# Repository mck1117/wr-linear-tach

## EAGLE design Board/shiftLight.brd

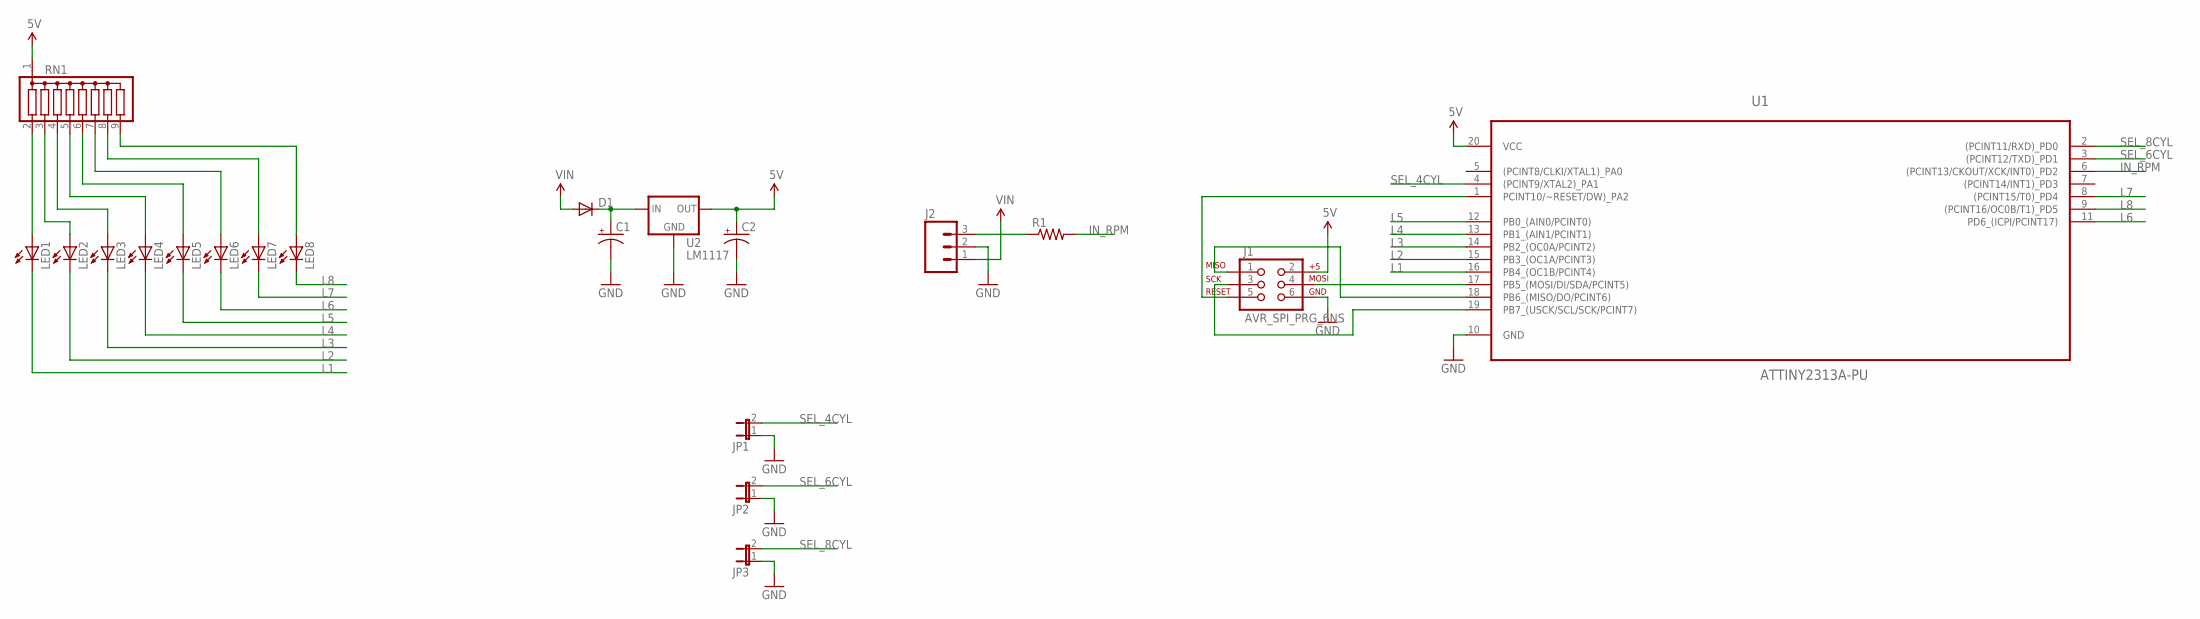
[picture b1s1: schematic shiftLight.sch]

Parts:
C1, C2: CPOL-USE3.5-8; E3,5-8
D1: DIODEPTH; DIODE-1N4001
J1: AVR_SPI_PRG_6NS; 2X3-NS
J2: M03SCREW; SCREWTERMINAL-3.5MM-3
JP1, JP2, JP3: JUMPER-2SMD-NO; SJ_2S-NO
LED1, LED2, LED3, LED4, LED5, LED6, LED7, LED8: LED5MM
R1: RESISTORPTH-1/4W; AXIAL-0.4
RN1: G08R; SIL9
U1: ATTINY2313A-PU; DIP254P762X533-20
U2: LM1117; TO-220-ALT

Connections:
5V: C2.+, J1.2, RN1.1, U1.20 (VCC), U2.OUT
GND: C1.-, C2.-, J1.6, J2.2, JP1.1, JP2.1, JP3.1, U1.10 (GND), U2.GND
IN_RPM: R1.P$2 (2), U1.6 ((PCINT13/CKOUT/XCK/INT0)_PD2)
L1: LED1.K (C), U1.16 (PB4_(OC1B/PCINT4))
L2: LED2.K (C), U1.15 (PB3_(OC1A/PCINT3))
L3: LED3.K (C), U1.14 (PB2_(OC0A/PCINT2))
L4: LED4.K (C), U1.13 (PB1_(AIN1/PCINT1))
L5: LED5.K (C), U1.12 (PB0_(AIN0/PCINT0))
L6: LED6.K (C), U1.11 (PD6_(ICPI/PCINT17))
L7: LED7.K (C), U1.8 ((PCINT15/T0)_PD4)
L8: LED8.K (C), U1.9 ((PCINT16/OC0B/T1)_PD5)
unnamed: LED1.A, RN1.2
unnamed: LED2.A, RN1.3
unnamed: LED3.A, RN1.4
unnamed: LED4.A, RN1.5
unnamed: LED5.A, RN1.6
unnamed: LED6.A, RN1.7
unnamed: LED7.A, RN1.8
unnamed: J2.3, R1.P$1 (1)
unnamed: C1.+, D1.C, U2.IN
unnamed: J1.4, U1.17 (PB5_(MOSI/DI/SDA/PCINT5))
unnamed: J1.3, U1.19 (PB7_(USCK/SCL/SCK/PCINT7))
unnamed: J1.1, U1.18 (PB6_(MISO/DO/PCINT6))
unnamed: J1.5, U1.1 (PCINT10/~RESET/DW)_PA2)
unnamed: LED8.A, RN1.9
SEL_4CYL: JP1.2, U1.4 ((PCINT9/XTAL2)_PA1)
SEL_6CYL: JP2.2, U1.3 ((PCINT12/TXD)_PD1)
SEL_8CYL: JP3.2, U1.2 ((PCINT11/RXD)_PD0)
VIN: D1.A, J2.1

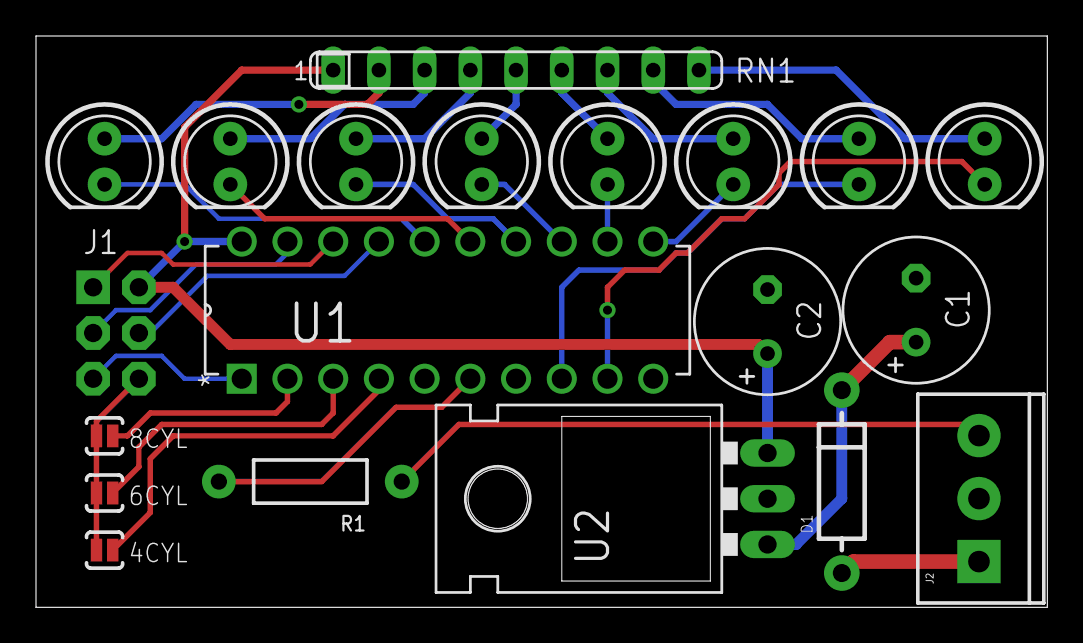
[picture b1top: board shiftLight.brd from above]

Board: 2 copper layers, 56.2 x 31.7 mm, 20 parts (0 on the bottom side), 29 nets.

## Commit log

2014-10-18 Add gitignore and gitattributes
2014-10-18 Add firmware files.
2014-10-18 Add Eagle gitignore
2014-10-18 Add LED test blink
2014-10-18 Add board design
2014-10-19 Update to functional firmware code
    - Remove cylinder count support
    - Correct LED output polarity (it's active low)
    - Ensure that RPM calculation only occurs on a rising edge
    - Adjust LED activation points

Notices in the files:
parts and their libraries:
SparkFun-LED: Licensing: CC v3.0 Share-Alike You are welcome to use this library for commercial purposes.
